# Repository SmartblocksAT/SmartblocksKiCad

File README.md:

# SmartblocksKiCad
These are the schematics-, assembly-, layout plans and other stuff for KiCad.

Smartblocks is a project by students at the [HTL-Waidhofen](https://htlwy.at/).

# Goal
The Goal is to develop a microcontroller environment for students, which should make it easy for them to start programming with microcontrollers.

We started this Project in February of 2019.
In this time a rough concept that defined the function and dimensions was created and presented to teachers who would later use this project. A proof of concept has been worked on in the summer in order to get an idea of ​​how the project could develop and look like.

As soon as the project was successfully submitted, the existing elements of the prototype, such as the web interface, sample programs and the practical structure, were revised and improved.

# Components
This Project consists of two Components:

 - The webinterface (can be found [here](https://github.com/SmartblocksAT/SmartblocksWeb))
 - ESP32 Library (can be found [here](https://github.com/SmartblocksAT/SmartblocksLibrary))
 - Schematics, etc. (this repository)

## Who is responsible for this?
Lukas Kamleitner <lukas.kamleitner@smartblocks.dev>

Maximilian Mernacher <maximilian.mernacher@smartblocks.dev>

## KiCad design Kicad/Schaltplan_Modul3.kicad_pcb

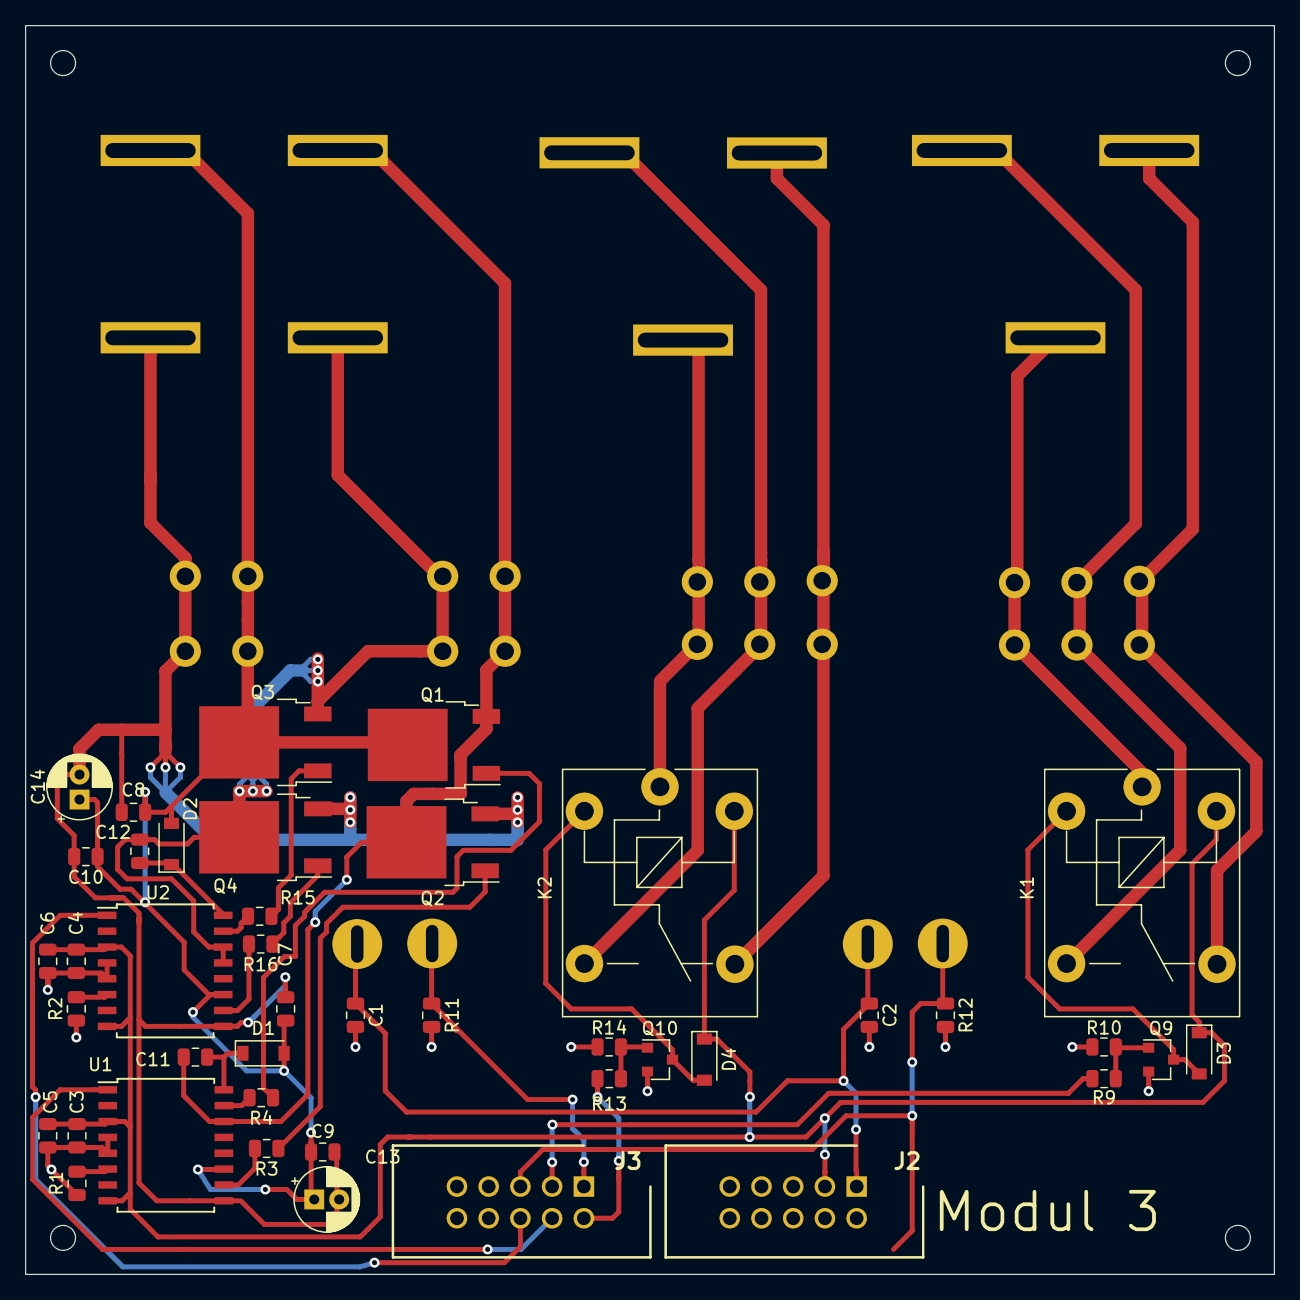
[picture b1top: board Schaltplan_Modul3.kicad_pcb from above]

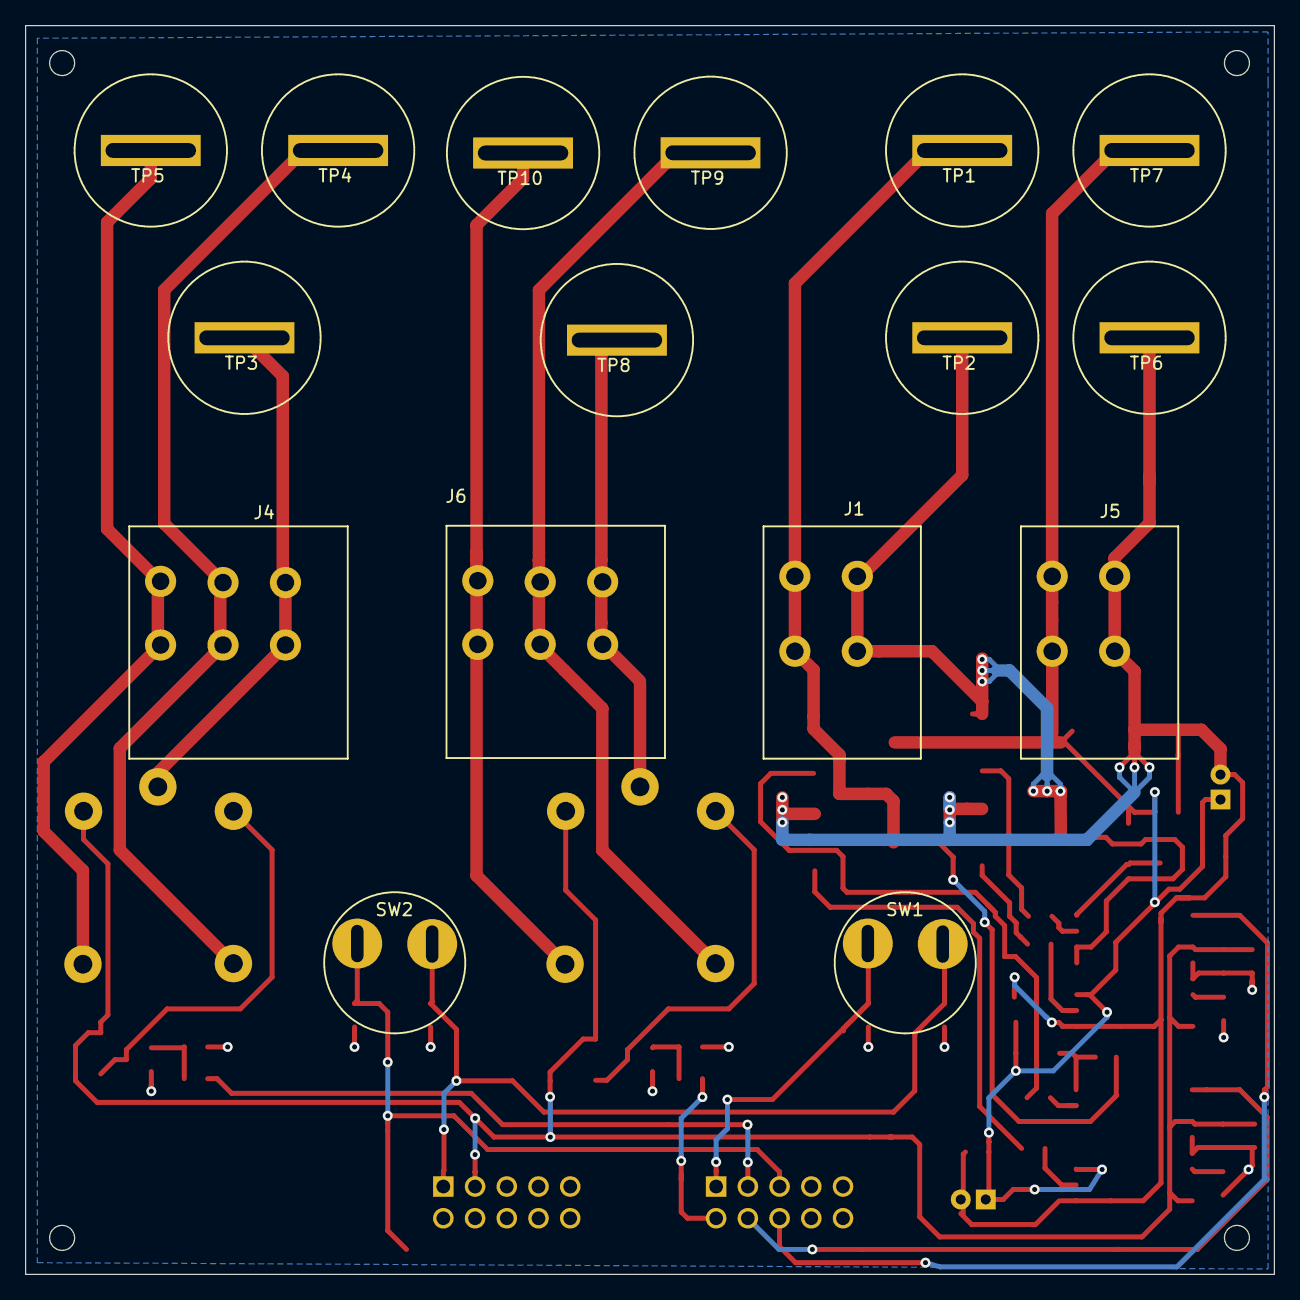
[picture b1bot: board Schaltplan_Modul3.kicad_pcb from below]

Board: 2 copper layers, 100.0 x 100.0 mm, 58 parts (16 on the bottom side), 35 nets.

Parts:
C1, C2: 10nF; C_0805_2012Metric
C3, C4, C9, C10: 100nF; C_0805_2012Metric
C5, C6, C7, C8, C11, C12: 1uF; C_0805_2012Metric
C13, C14: 10uF; CP_Radial_D5.0mm_P2.00mm
D1, D2, D3, D4: 1N4148; D_SOD-123
J1: Mosfets; TBL_127B 2
J2: ConnectorBUS_Rechts; SHDR10W64P254X254_2X5_2032X880X915P
J3: Connector_Rechts; SHDR10W64P254X254_2X5_2032X880X915P
J4, J6: Relais; TBL_127B 3
J5: Versorgung; TBL_127B 2
K1, K2: SANYOU_SRD_Form_C; Relay_SPDT_SANYOU_SRD_Series_Form_C
Q1, Q2, Q3, Q4: NVD5C454NT4G; TO-252-2
Q9, Q10: BC817; SOT-23
R1, R2: 100K; R_0805_2012Metric
R3, R4, R15, R16: 100R; R_0805_2012Metric
R9, R13: 5K6; R_0805_2012Metric
R10, R11, R12, R14: 10K; R_0805_2012Metric
SW1, SW2: SW_DIP_x01; Druckschalter
TP1, TP2: Geschalteter; BannaJack
TP3, TP8: 11; BannaJack
TP4, TP9: 14; BannaJack
TP5, TP10: 13; BannaJack
TP6: GND_Bannannenstecker; BannaJack
TP7: 6V-24VBannannenstecker; BannaJack
U1, U2: si8234bb; SOIC-16W_7.5x10.3mm_P1.27mm

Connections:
+3V3: C1.1, C2.1, J2.1, SW1.1, SW2.1
+5V: C3.1, C4.1, C5.1, C6.1, D3.1, D4.1, J2.3, K1.5, K2.5, U1.3, U1.8, U2.3, U2.8
+12V: C7.1, C8.1, C9.1, C10.1, C13.1, C14.1, D1.2, D2.2, J5.1, Q1.2, Q3.2, TP7.1, U1.11, U2.11
/IO2: J3.1, R11.1, SW1.2
/IO4: J3.2, R13.1
/IO13: J3.3, R9.1
/IO16: J3.4, U1.1
/IO17: J3.6, U2.1
/IO32: J3.5, R12.1, SW2.2
GND: C1.2, C2.2, C3.2, C4.2, C5.2, C6.2, J2.2, Q9.2, Q10.2, R1.1, R2.1, R10.2, R11.2, R12.2, R14.2, U1.4, U1.5, U2.4, U2.5
GNDS: C7.2, C8.2, C9.2, C10.2, C13.2, C14.2, J5.2, Q2.3, Q4.3, TP6.1, U1.9, U2.9
unnamed: C11.1, D1.1, U1.16
unnamed: C11.2, J1.1, Q1.3, Q2.2, TP1.1, U1.14
unnamed: C12.1, D2.1, U2.16
unnamed: C12.2, J1.2, Q3.3, Q4.2, TP2.1, U2.13, U2.14
unnamed: D3.2, K1.2, Q9.3
unnamed: D4.2, K2.2, Q10.3
unnamed: J4.1, K1.4, TP5.1
unnamed: J4.2, K1.3, TP4.1
unnamed: J4.3, K1.1, TP3.1
unnamed: J6.1, K2.4, TP10.1
unnamed: J6.2, K2.3, TP9.1
unnamed: J6.3, K2.1, TP8.1
unnamed: Q1.1, R4.1
unnamed: Q2.1, R3.1
unnamed: Q3.1, R15.1
unnamed: Q4.1, R16.1
unnamed: Q9.1, R9.2, R10.1
unnamed: Q10.1, R13.2, R14.1
unnamed: R1.2, U1.6
unnamed: R2.2, U2.6
unnamed: R3.2, U1.10
unnamed: R4.2, U1.15
unnamed: R15.2, U2.15
unnamed: R16.2, U2.10

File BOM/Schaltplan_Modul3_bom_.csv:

Component,Description,Part,References,Value,Footprint,Quantity Per PCB,Datasheet
1,Unpolarized capacitor,C,C3 C4 C9 C10,100nF,C_0805_2012Metric,4,Capacitor 0805 100nF
2,Unpolarized capacitor,C,C1 C2,10nF,C_0805_2012Metric,2,Capacitor 0805 10nF
3,Polarised capacitor,CP,C13 C14,10uF,CP_Radial_D5.0mm_P2.00mm,2,Capacitor 0805 10uF
4,Unpolarized capacitor,C,C5 C6 C7 C8 C11 C12,1uF,C_0805_2012Metric,6,Capacitor 0805 1uF
5,"100V 0.15A standard switching diode, DO-35",1N4148,D1 D2 D3 D4,1N4148,D_SOD-123,4,1N4148
6,"Generic connector, double row, 02x05, odd/even pin numbering scheme (row 1 odd numbers, row 2 even numbers), script generated (kicad-library-utils/schlib/autogen/connector/)",Conn_02x05_Odd_Even,J2,ConnectorBUS_Rechts,SHDR10W64P254X254_2X5_2032X880X915P,1,Stecker Messerleiste  WSL 10G
7,"Generic connector, double row, 02x03, odd/even pin numbering scheme (row 1 odd numbers, row 2 even numbers), script generated (kicad-library-utils/schlib/autogen/connector/)",Conn_02x03_Odd_Even,J3,Connector_Rechts,SHDR10W64P254X254_2X5_2032X880X915P,1,Stecker Messerleiste  WSL 10G
8,"Generic screw terminal, single row, 01x02, script generated (kicad-library-utils/schlib/autogen/connector/)",Screw_Terminal_01x02,J1 J5,Mosfets,TBL_127B 2,2,TBL 127B p2
9,"Generic screw terminal, single row, 01x03, script generated (kicad-library-utils/schlib/autogen/connector/)",Screw_Terminal_01x03,J4 J6,Relais,TBL_127B 3,2,TBL 127B p3
10,"Sanyo SRD relay, Single Pole Miniature Power Relay,",SANYOU_SRD_Form_C,K1 K2,SANYOU_SRD_Form_C,Relay_SPDT_SANYOU_SRD_Series_Form_C,2,SANYOU_SRD_Form_C
11,"0.8A Ic, 45V Vce, NPN Transistor, SOT-23",BC817,Q9 Q10,BC817,SOT-23,2,BC817 SOT-23
12,Transistor N-MOSFET with substrate diode (general),Q_NMOS_GDS,Q1 Q2 Q3 Q4,NVD5C454NT4G,TO-252-2,4,NVD5C454NT4G TO-252-2
13,Resistor,R,R1 R2,100K,R_0805_2012Metric,2,Resistor 0805 100k
14,Resistor,R,R3 R4,100R,R_0805_2012Metric,2,Resistor 0805 100R
15,Resistor,R,R10 R11 R12 R14,10K,R_0805_2012Metric,4,Resistor 0805 10k
16,Resistor,R,R9 R13,5K6,R_0805_2012Metric,2,Resistor 0805 5k6
17,"1x DIP Switch, Single Pole Single Throw (SPST) switch, small symbol",SW_DIP_x01,SW1 SW2,SW_DIP_x01,Druckschalter,2,B077FH7TGD Taster
18,,si8234bb,U1 U2,si8234bb,SOIC-16W_7.5x10.3mm_P1.27mm,2,si8234bb SOIC-16W





Component Groups:,18
Component Count:,46
Fitted Components:,46
Number of PCBs:,1
Total components:,46
Schematic Version:,
Schematic Date:,
PCB Variant:,[u'default']
BoM Date:,15.03.2020 15:04:35
Schematic Source:,Schaltplan_Modul3.sch
KiCad Version:,Eeschema (5.0.0)

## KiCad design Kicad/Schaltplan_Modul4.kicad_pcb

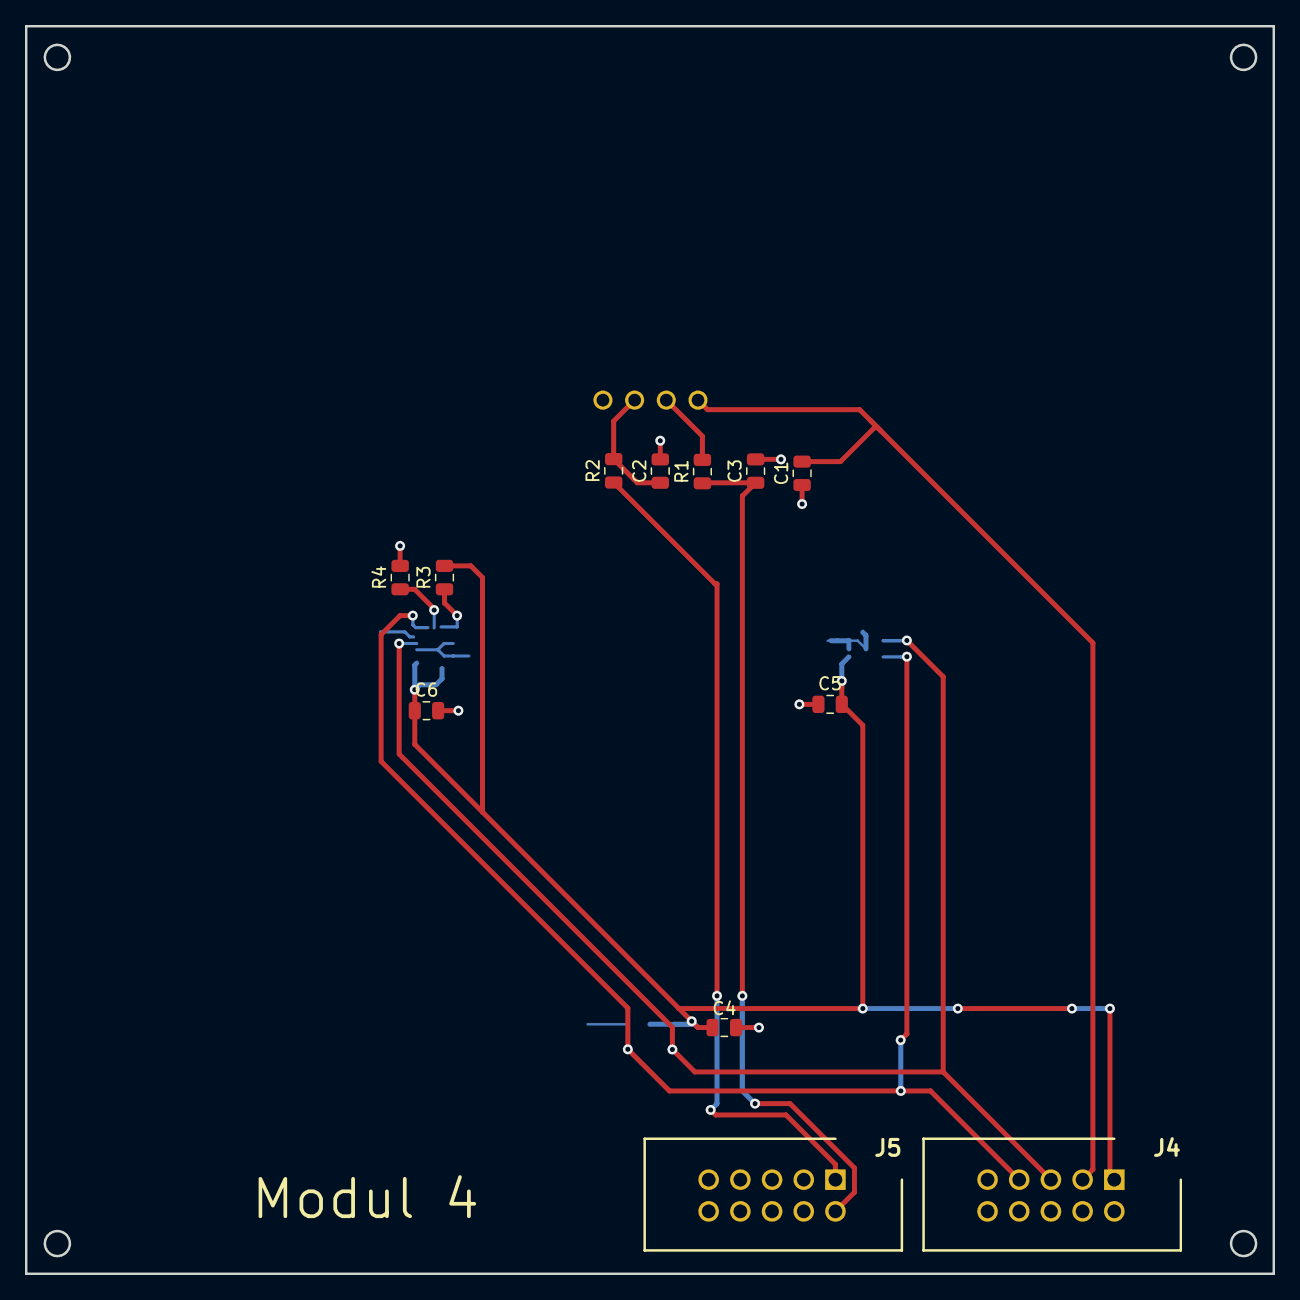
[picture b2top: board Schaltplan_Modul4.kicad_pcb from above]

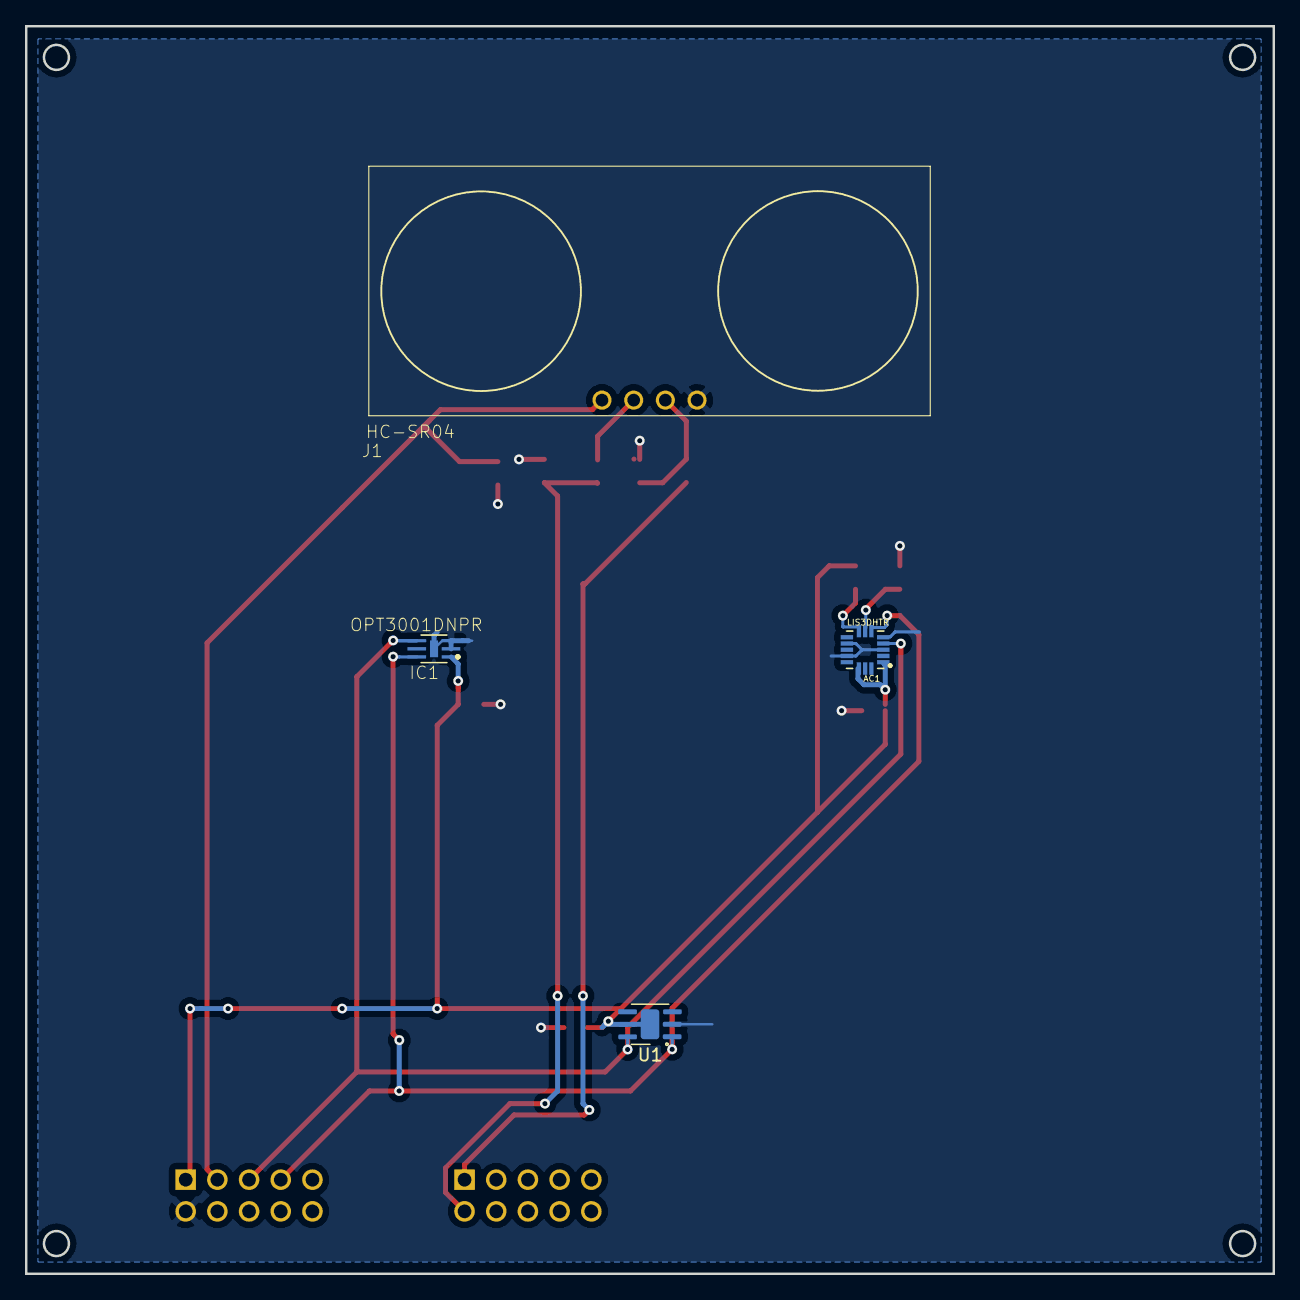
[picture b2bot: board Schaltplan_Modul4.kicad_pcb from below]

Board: 2 copper layers, 100.0 x 100.0 mm, 16 parts (4 on the bottom side), 11 nets.

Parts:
AC1: LIS3DHTR; XDCR_LIS3DHTR
C1, C4, C5, C6: 1pF; C_0805_2012Metric
C2, C3: 47pF; C_0805_2012Metric
IC1: OPT3001DNPR
J1: HC-SR04; XCVR_HC-SR04
J4: ConnectorBUS_Rechts; SHDR10W64P254X254_2X5_2032X880X915P
J5: Conn_02x01; SHDR10W64P254X254_2X5_2032X880X915P
R1, R2: 47R; R_0805_2012Metric
R3, R4: 10K; R_0805_2012Metric
U1: Si7020-A20; DFN-6-1EP_3x3mm_P1mm_EP1.5x2.4mm

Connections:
+3V3: AC1.1, AC1.14, C4.1, C5.2, C6.1, IC1.1, J4.1, R3.2, U1.5, U1.7
+5V: C1.2, J1.1, J4.3
/IO14: J5.1, R2.1
/IO27: C3.1, J5.2, R1.1
/SCL: AC1.4, IC1.4, J4.5, U1.6
/SDA: AC1.6, IC1.6, J4.7, U1.1
GND: AC1.3, AC1.5, AC1.10, AC1.12, C1.1, C2.2, C3.2, C4.2, C5.1, C6.2, IC1.2, IC1.3, IC1.7, J1.4, J4.2, R4.2, U1.2
unnamed: AC1.7, R4.1
unnamed: AC1.8, R3.1
unnamed: C2.1, J1.3, R2.2
unnamed: J1.2, R1.2

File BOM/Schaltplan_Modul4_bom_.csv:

Component,Description,Part,References,Value,Footprint,Quantity Per PCB,Datasheet
1,"Accelerometer 3-Axis 2g/16g 1.8V LGA16 STMicroelectronics LIS3DHTR Accelerometer IC, 3-axis, I2C, SPI 1.71  3.6 V, 16-Pin LGA",LIS3DHTR,AC1,LIS3DHTR,XDCR_LIS3DHTR,1,LIS3DHTR LGA-16 
2,Unpolarized capacitor,C,C1 C4 C5 C6,1pF,C_0805_2012Metric,4,Capacitor 0805 1pF
3,Unpolarized capacitor,C,C2 C3,47pF,C_0805_2012Metric,2,Capacitor 0805 1pF
4,Digital Ambient Light Sensor (ALS) With High-Precision Human-Eye Response,OPT3001DNPR,IC1,OPT3001DNPR,OPT3001DNPR,1,OPT3001DNPR USON-6 
5,"Generic connector, double row, 02x01, this symbol is compatible with counter-clockwise, top-bottom and odd-even numbering schemes., script generated (kicad-library-utils/schlib/autogen/connector/)",Conn_02x01,J5,Conn_02x01,SHDR10W64P254X254_2X5_2032X880X915P,1,Stecker Messerleiste  WSL 10G
6,"Generic connector, double row, 02x05, odd/even pin numbering scheme (row 1 odd numbers, row 2 even numbers), script generated (kicad-library-utils/schlib/autogen/connector/)",Conn_02x05_Odd_Even,J4,ConnectorBUS_Rechts,SHDR10W64P254X254_2X5_2032X880X915P,1,Stecker Messerleiste  WSL 10G
7,,HC-SR04,J1,HC-SR04,XCVR_HC-SR04,1,HC-SR04
8,Resistor,R,R3 R4,10K,R_0805_2012Metric,2,Resistor 0805 10k
9,Resistor,R,R1 R2,47R,R_0805_2012Metric,2,Resistor 0805 47R
10,"I2C Humidity and Temperature Sensor, DFN-6",Si7020-A20,U1,Si7020-A20 DFN-6,DFN-6-1EP_3x3mm_P1mm_EP1.5x2.4mm,1,Si7020-A20 DFN_QFN





Component Groups:,10
Component Count:,16
Fitted Components:,16
Number of PCBs:,1
Total components:,16
Schematic Version:,
Schematic Date:,
PCB Variant:,[u'default']
BoM Date:,15.03.2020 14:37:53
Schematic Source:,Schaltplan_Modul4.sch
KiCad Version:,Eeschema (5.0.0)

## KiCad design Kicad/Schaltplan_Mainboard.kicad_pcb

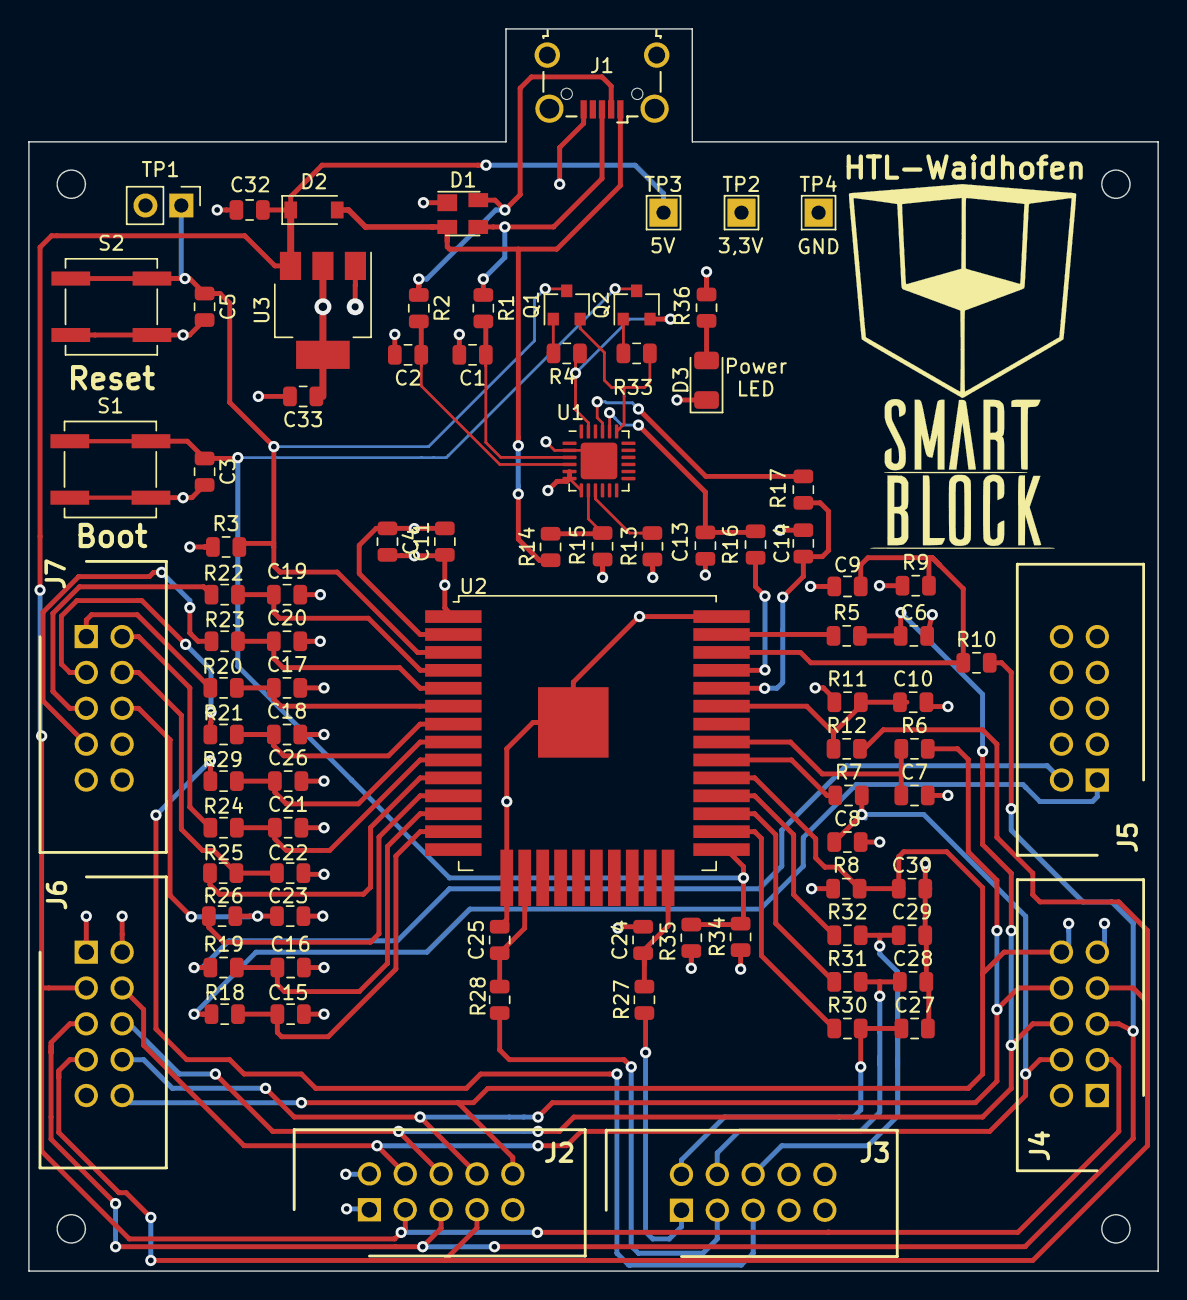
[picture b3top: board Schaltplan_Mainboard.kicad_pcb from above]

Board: 4 copper layers, 80.0 x 88.0 mm, 88 parts (0 on the bottom side), 62 nets.

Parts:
C1, C2, C6, C7, C8, C9, C10, C13, C14, C15, C16, C17, C18, C19, C20, C21, C22, C23, C24, C25, C26, C27, C28, C29, C30: 47pF; C_0805_2012Metric
C3, C5: 0,1nF; C_0805_2012Metric
C4, C11, C32, C33: 1uF; C_0805_2012Metric
D1: SP0503BAHT; SOT-143
D2: 1N5819HW-7-F; D_SOD-123
D3: Led Spannung; LED_1206_3216Metric
J1: Micro-B_Wuerth_629105150521; USB_Micro-B_Wuerth_629105150521_CircularHoles
J2: ConnectorBUS_Front; SHDR10W64P254X254_2X5_2032X880X915P
J3: Connector_Front; SHDR10W64P254X254_2X5_2032X880X915P
J4: ConnectorBUS_Rechts; SHDR10W64P254X254_2X5_2032X880X915P
J5: Conn_Rechts; SHDR10W64P254X254_2X5_2032X880X915P
J6: ConnectorBUS_Links; SHDR10W64P254X254_2X5_2032X880X915P
J7: Connector_Links; SHDR10W64P254X254_2X5_2032X880X915P
Q1, Q2: BC817; SOT-23
R1, R2: 22R; R_0805_2012Metric
R3, R4, R8, R33, R34: 10K; R_0805_2012Metric
R5, R6, R7, R10, R12, R16, R17, R18, R19, R20, R21, R22, R23, R24, R25, R26, R27, R28, R29, R30, R31, R32: R47; R_0805_2012Metric
R9, R11: 4K7; R_0805_2012Metric
R13: 2K; R_0805_2012Metric
R14: 22,1K; R_0805_2012Metric
R15: 47,5k; R_0805_2012Metric
R35: 1M NC; R_0805_2012Metric
R36: 300R; R_0805_2012Metric
S1: BOOT Option; SW_SPST_B3SL-1002P
S2: Reset; SW_SPST_B3SL-1002P
TP1: Externer Reset; PinHeader_1x02_P2.54mm_Vertical
TP2: TestPoint 5V; TestPoint_THTPad_2.0x2.0mm_Drill1.0mm
TP3: TestPoint 3,3V; TestPoint_THTPad_2.0x2.0mm_Drill1.0mm
TP4: TestPoint GND; TestPoint_THTPad_2.0x2.0mm_Drill1.0mm
U1: CP2102N-A01-GQFN24; QFN-24-1EP_4x4mm_P0.5mm_EP2.6x2.6mm
U2: EP32-WROOM-32D; ESP32-WROOM-32U
U3: AMS1117-3.3; SOT-223-3_TabPin2

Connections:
+3V3: C4.1, C11.2, C33.1, J2.1, J4.1, J6.1, R3.1, R8.1, R9.1, R11.1, R13.1, R34.1, R36.1, TP2.1, U1.5, U1.6, U1.7, U2.2, U3.2
+5V: C32.1, D2.1, J2.3, J4.3, J6.3, TP3.1, U3.3
/DTR: Q2.2, R4.2, U1.23
/IO2: C24.1, R27.1, U2.24
/IO4: R30.1, U2.26
/IO13: C25.1, R28.1, U2.16
/IO14: C15.1, R18.1, U2.13
/IO16: R31.1, U2.27
/IO17: R32.1, U2.28
/IO25: R25.1, U2.10
/IO26: R26.1, U2.11
/IO27: C16.1, R19.2, U2.12
/IO32: C26.1, R29.1, U2.8
/IO33: C21.1, R24.1, U2.9
/IO34: C17.1, R20.1, U2.6
/IO35: C18.1, R21.1, U2.7
/IO36: C19.1, R22.1, U2.4
/IO39: C20.1, R23.1, U2.5
/RTS: Q1.2, R33.2, U1.19
/RXD: R16.2, U2.35
/SCL: J2.5, J4.5, J6.5, R10.2
/SCL_Raw: C9.1, R9.2, R10.1, U2.36
/SDA: J2.7, J4.7, J6.7, R12.2
/SDA_Raw: C10.1, R11.2, R12.1, U2.33
/TXD: C14.1, R17.2, U2.34
/USB1_DN: C2.1, R2.2, U1.4
/USB1_DP: C1.1, R1.2, U1.3
/VSPI_CLK: C8.1, J2.4, J4.4, J6.4, R7.2
/VSPI_CLK_Raw: R7.1, U2.30
/VSPI_CS: C30.1, J2.10, J4.10, J6.10, R8.2, U2.29
/VSPI_MISO: J2.8, J4.8, J6.8, R6.2
/VSPI_MISO_Raw: C7.1, R6.1, U2.31
/VSPI_MOSI: C6.1, J2.6, J4.6, J6.6, R5.2
/VSPI_MOSI_Raw: R5.1, U2.37
EN: C5.1, Q1.3, R3.2, S2.1, TP1.1, U2.3
GND: C1.2, C2.2, C3.2, C4.2, C5.2, C6.2, C7.2, C8.2, C9.2, C10.2, C11.1, C13.2, C14.2, C15.2, C16.2, C17.2, C18.2, C19.2, C20.2, C21.2, C22.2, C23.2, C24.2, C25.2, C26.2, C27.2, C28.2, C29.2, C30.2, C32.2, C33.2, D1.1, D3.1, J1.5, J2.2, J4.2, J6.2, R15.2, R35.2, S1.2, S2.2, TP1.2, TP4.1, U1.2, U1.25, U2.1, U2.15, U2.38, U2.39, U3.1
IO0: C3.1, Q2.3, R34.2, R35.1, S1.1, U2.25
unnamed: C13.1, R16.1, U1.20
unnamed: C22.1, J7.4, R25.2
unnamed: C23.1, J7.6, R26.2
unnamed: C27.1, J3.2, R30.2
unnamed: C28.1, J3.4, R31.2
unnamed: C29.1, J3.6, R32.2
unnamed: D1.3, J1.3, R1.1
unnamed: D1.4, J1.2, R2.1
unnamed: D3.2, R36.2
unnamed: J3.1, R27.2
unnamed: J3.3, R28.2
unnamed: J3.5, R29.2
unnamed: J5.1, R18.2
unnamed: J5.2, R19.1
unnamed: J7.1, R20.2
unnamed: J7.2, R24.2
unnamed: J7.3, R21.2
unnamed: J7.5, R22.2
unnamed: J7.7, R23.2
unnamed: Q1.1, R4.1
unnamed: Q2.1, R33.1
unnamed: R13.2, U1.9
unnamed: R14.2, R15.1, U1.8
unnamed: R17.1, U1.21
VBUS: D1.2, D2.2, J1.1, R14.1

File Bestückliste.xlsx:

Referenz | Wert | Footprint | Anzahl | Sonsitges
C1 C2 C6 C7 C8 C9 C10 C13 C14 C15 C16 C17 C18 C19 C20 C21 C22 C23 C24 C25 C26 C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 | 47pF | C_0805_2012Metric | 25 | Capacitor 0805 47pF
C3 C5 | 100pF | C_0805_2012Metric | 2 | Capacitor 0805 100pF
C4 C11 C32 C33 | 1uF | C_0805_2012Metric | 4 | Capacitor 0805 1uF
D1 | SP0503BAHT | SOT-143 | 1 | SP0503BAHT SOT-143
D2 | 1N5819HW-7-F | SOD 123 | 1 | 1N5819HW-7-F SOD-123
D3 | Led Smd 1206 | LED_1206_3216Metric | 1 | Led Smd 1206
J1 | Micro-B_Wuerth_629105150521 | USB_Micro-B_Wuerth_629105150521_CircularHoles | 1 | USB B Micro-B_Wuerth_629105150521
J2 J4 J6 | Stecker Messerleiste WSL 10G | SHDR10W64P254X254_2X5_2032X880X915P | 3 | Stecker Messerleiste WSL 10G
J3 | Stecker Messerleiste WSL 10G | SHDR10W64P254X254_2X5_2032X880X915P | 1 | Stecker Messerleiste WSL 10G
J5 | Stecker Messerleiste WSL 10G | SHDR10W64P254X254_2X5_2032X880X915P | 1 | Stecker Messerleiste WSL 10G
J7 | Stecker Messerleiste WSL 10G | SHDR10W64P254X254_2X5_2032X880X915P | 1 | Stecker Messerleiste WSL 10G
Q1 Q2 | BC817 | SOT-23 | 2 | BC817 SOT-23
R1 R2 | 22R | R_0805_2012Metric | 2 | Resistor 0805 22R
R13 | 2k2 | R_0805_2012Metric | 1 | Resistor 0805 2k2
R14 | 22,1k | R_0805_2012Metric | 1 | Resistor 0805 22,1k
R15 | 47,5k | R_0805_2012Metric | 1 | Resistor 0805 47,5k
R3 R4 R8 R33 R34 | 10k | R_0805_2012Metric | 5 | Resistor 0805 10k
R35 | 1M | R_0805_2012Metric | 1 | Resistor 0805 1M
R36 | 330R | R_0805_2012Metric | 1 | Resistor 0805 330R
R5 R6 R7 R10 R12 R16 R17 R18 R19 R20 R21 R22 R23 R24 R25 R26 R27 R28 R29 R30 R3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 | 47R | R_0805_2012Metric | 22 | Resistor 0805 47R
R9 R11 | 4k7 | R_0805_2012Metric | 2 | Resistor 0805 4k7
S1 | B3SL-1002P | SW_SPST_B3SL-1002P | 1 | Button SMD B3SL-1002P
S2 | B3SL-1002P | SW_SPST_B3SL-1002P | 1 | Button SMD B3SL-1002P
U1 | CP2102N-A01-GQFN24 | QFN-24-1EP_4x4mm_P0.5mm_EP2.6x2.6mm | 1 | CP2102N-A01-G QFN24
U2 | EP32-WROOM-32D | ESP32-WROOM-32U | 1 | EP32-WROOM-32D
U3 | AMS1117-3.3 | SOT-223-3_TabPin2 | 1 | AMS1117-3.3 SOT-223-3
Mainboard

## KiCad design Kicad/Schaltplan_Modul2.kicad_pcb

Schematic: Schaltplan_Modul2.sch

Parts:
C1, C2, C3, C4, C5: 10nF; C_0805_2012Metric
D1, D2, D3: Led THT; D_DO-15_P5.08mm_Vertical_KathodeUp
J1: ConnectorBUS_Front; SHDR10W64P254X254_2X5_2032X880X915P
J2: Connector_Front; SHDR10W64P254X254_2X5_2032X880X915P
J3: LCD Dobrovitz; LCD_dobro
Q1: BC817; SOT-23
R1, R2, R6, R8: 10k; R_0805_2012Metric
R3, R5, R7: 220R; R_0805_2012Metric
RV1: R_POT 10k; Potentiometer_Bourns_3314G_Vertical
SW1, SW3, SW4: SW_DIP_x01; Druckschalter
U1: PCF8574; SOIC-16W_7.5x10.3mm_P1.27mm

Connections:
+3V3: C2.1, C4.1, C5.1, J1.1, SW1.1, SW3.1, SW4.1
+5V: C1.2, J1.3, J3.2, J3.16, RV1.1, U1.16 (VDD)
/IO2: J2.1, R1.1, SW1.2
/IO4: J2.2, R3.1
/IO13: J2.3, R6.1, SW3.2
/IO16: J2.4, R5.1
/IO17: J2.6, R7.1
/IO32: J2.5, R8.1, SW4.2
/SCL: J1.5, U1.14 (SCL)
/SDA: J1.7, U1.15 (SDA)
/VSPI_CLK: J1.4
/VSPI_CS: J1.10
/VSPI_MISO: J1.8
/VSPI_MOSI: J1.6
GND: C1.1, C2.2, C3.1, C4.2, C5.2, D1.1, D2.1, D3.1, J1.2, J3.1, Q1.2, R1.2, R6.2, R8.2, RV1.3, U1.1 (A0), U1.2 (A1), U1.3 (A2), U1.8 (VSS)
unnamed: C3.2, R2.1, U1.7 (P3)
unnamed: D1.2, R3.2
unnamed: D2.2, R5.2
unnamed: D3.2, R7.2
unnamed: J3.3, RV1.2
unnamed: J3.4, U1.4 (P0)
unnamed: J3.5, U1.5 (P1)
unnamed: J3.6, U1.6 (P2)
unnamed: J3.11, U1.9 (P4)
unnamed: J3.12, U1.10 (P5)
unnamed: J3.13, U1.11 (P6)
unnamed: J3.14, U1.12 (P7)
unnamed: J3.15, Q1.3
unnamed: Q1.1, R2.2

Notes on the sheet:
Modul 2
LCD i2C
Stecker
LEDs
Taster

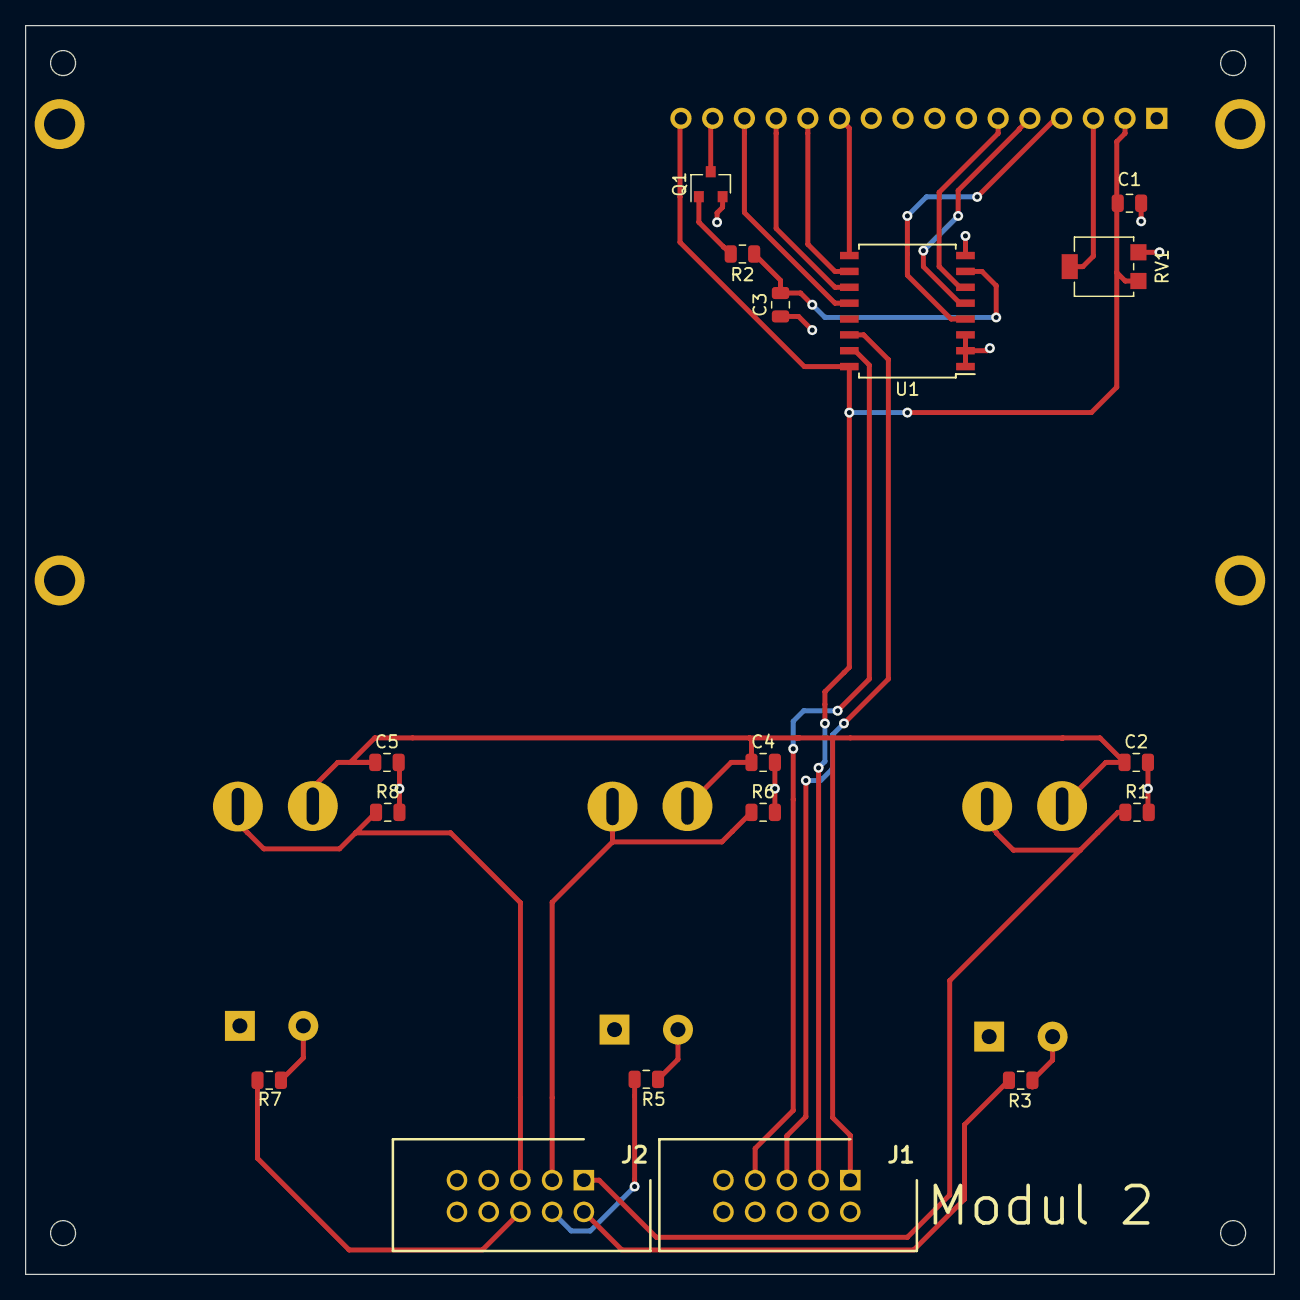
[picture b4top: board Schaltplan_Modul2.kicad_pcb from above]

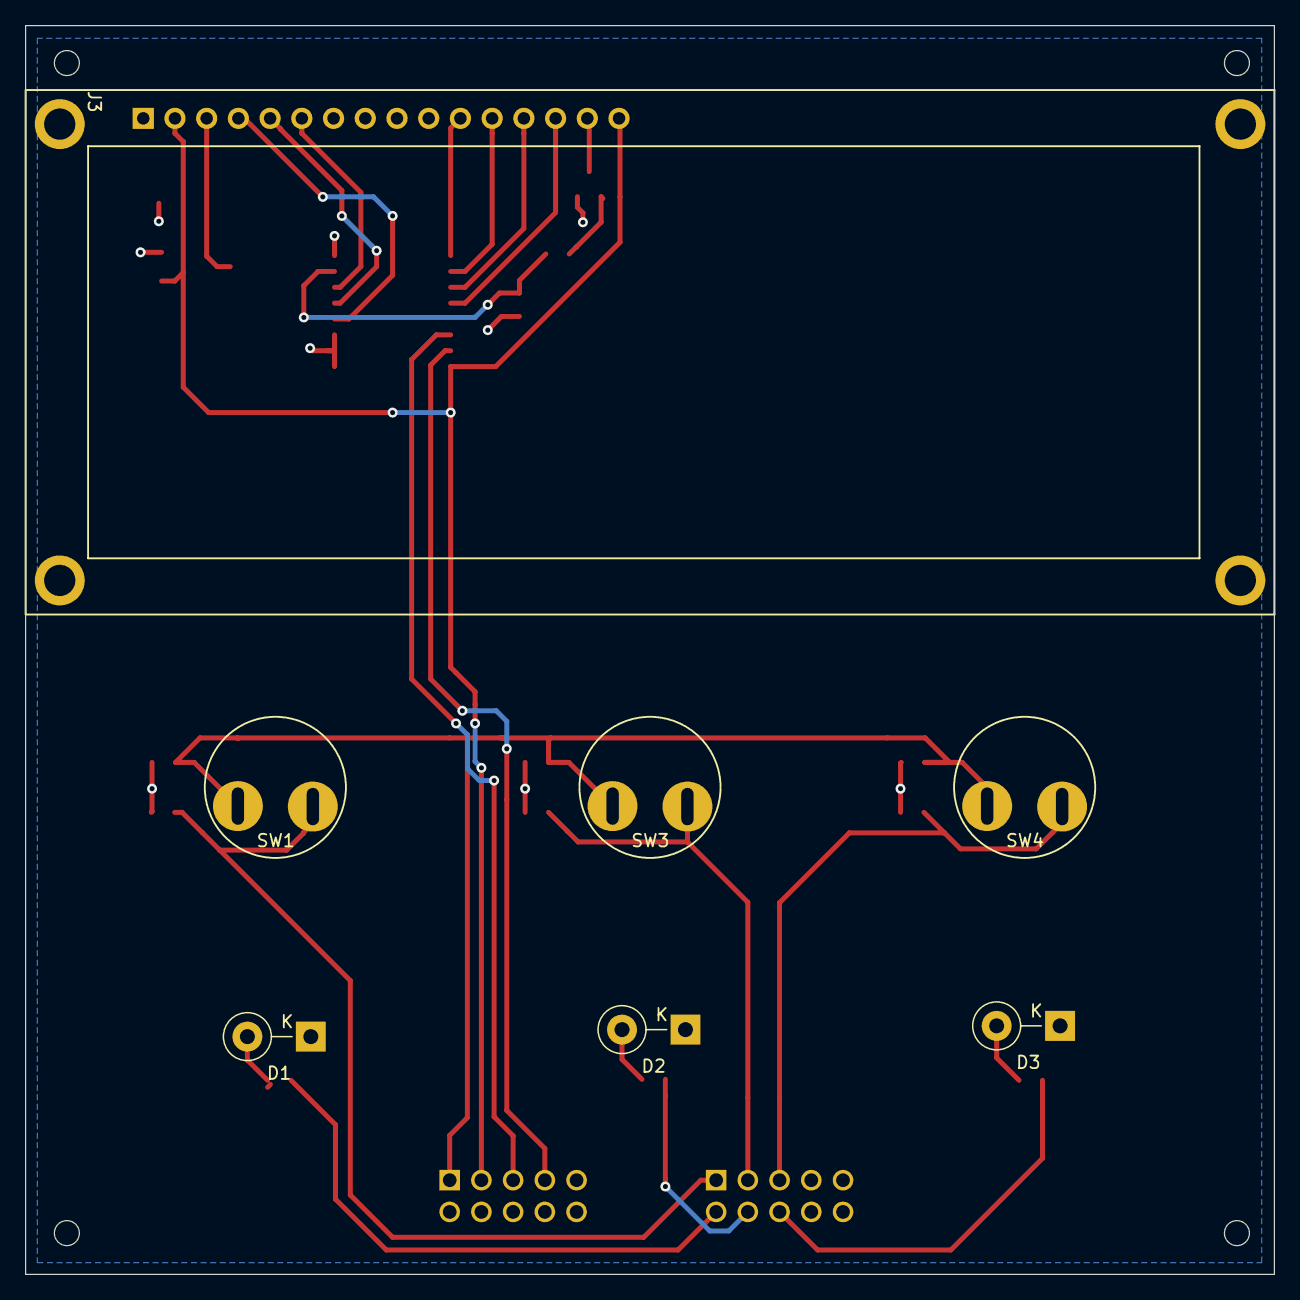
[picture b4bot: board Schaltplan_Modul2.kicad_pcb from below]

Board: 2 copper layers, 100.0 x 100.0 mm, 24 parts (7 on the bottom side), 25 nets.

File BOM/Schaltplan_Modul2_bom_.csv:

Component,Description,Part,References,Value,Footprint,Quantity Per PCB,Datasheet
1,Unpolarized capacitor,C,C1 C2 C3 C4 C5,10nF,C_0805_2012Metric,5,Capacitor 0805 10nF
2,LED generic,LED,D1 D2 D3,Led THT,D_DO-15_P5.08mm_Vertical_KathodeUp,3,Led Smd 1206 d5mm
3,"Generic connector, double row, 02x05, odd/even pin numbering scheme (row 1 odd numbers, row 2 even numbers), script generated (kicad-library-utils/schlib/autogen/connector/)",Conn_02x05_Odd_Even,J1,ConnectorBUS_Front,SHDR10W64P254X254_2X5_2032X880X915P,1,Stecker Messerleiste  WSL 10G
4,"Generic connector, double row, 02x03, odd/even pin numbering scheme (row 1 odd numbers, row 2 even numbers), script generated (kicad-library-utils/schlib/autogen/connector/)",Conn_02x03_Odd_Even,J2,Connector_Front,SHDR10W64P254X254_2X5_2032X880X915P,1,Stecker Messerleiste  WSL 10G
5,"Generic connector, single row, 01x16, script generated (kicad-library-utils/schlib/autogen/connector/)",Conn_01x16_Male,J3,LCD Dobrovitz,LCD_dobro,1,LCD Dobrovitz
6,"0.8A Ic, 45V Vce, NPN Transistor, SOT-23",BC817,Q1,BC817,SOT-23,1,BC817 SOT-23
7,Resistor,R,R1 R2 R6 R8,10k,R_0805_2012Metric,4,Resistor 0805 10k
8,Resistor,R,R3 R5 R7,220R,R_0805_2012Metric,3,Resistor 0805 220R
9,Potentiometer,R_POT,RV1,R_POT 10k,Potentiometer_Bourns_3314G_Vertical,1,R_POT 10k Bourns_3314G_Vertical
10,"1x DIP Switch, Single Pole Single Throw (SPST) switch, small symbol",SW_DIP_x01,SW1 SW3 SW4,SW_DIP_x01,Druckschalter,3,B077FH7TGD Taster
11,"8 Bit Port/Expander to I2C Bus, DIP/SOIC-16",PCF8574A,U1,PCF8574,SOIC-16W_7.5x10.3mm_P1.27mm,1,PCF8574AT SOIC-16W





Component Groups:,11
Component Count:,24
Fitted Components:,24
Number of PCBs:,1
Total components:,24
Schematic Version:,
Schematic Date:,
PCB Variant:,[u'default']
BoM Date:,15.03.2020 14:37:44
Schematic Source:,Schaltplan_Modul2.sch
KiCad Version:,Eeschema (5.0.0)

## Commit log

2020-03-26 Erster commit. Es wurden die benötigten KiCAD Dateien hinzugefügt.
2020-03-26 Update README.md
    Added basic information to the readme.
2020-03-26 Delete Bestückliste.xlsx
    Deleted due to internal changes.
2020-03-30 Added Parts list
2020-03-30 Smartbocks.pdf and Stückliste.xlsx were outdated.
2020-04-02 Pinout
